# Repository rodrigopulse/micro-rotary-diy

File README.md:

# Micro Rotary

## How to Use:

1. Clone or download this repository.
2. Customize the `platformio.ini` file with your board settings.
3. Use PlatformIO CLI to compile, upload, and debug the firmware.

## Useful Commands

### Creating configuration files for VS Code:

```shell
platformio init --ide vscode
```

### Installing dependency libraries

```shell
pio run
```

### Uploading to Arduino

```shell
pio run --target upload
```

### Monitor

```shell
pio device monitor
```

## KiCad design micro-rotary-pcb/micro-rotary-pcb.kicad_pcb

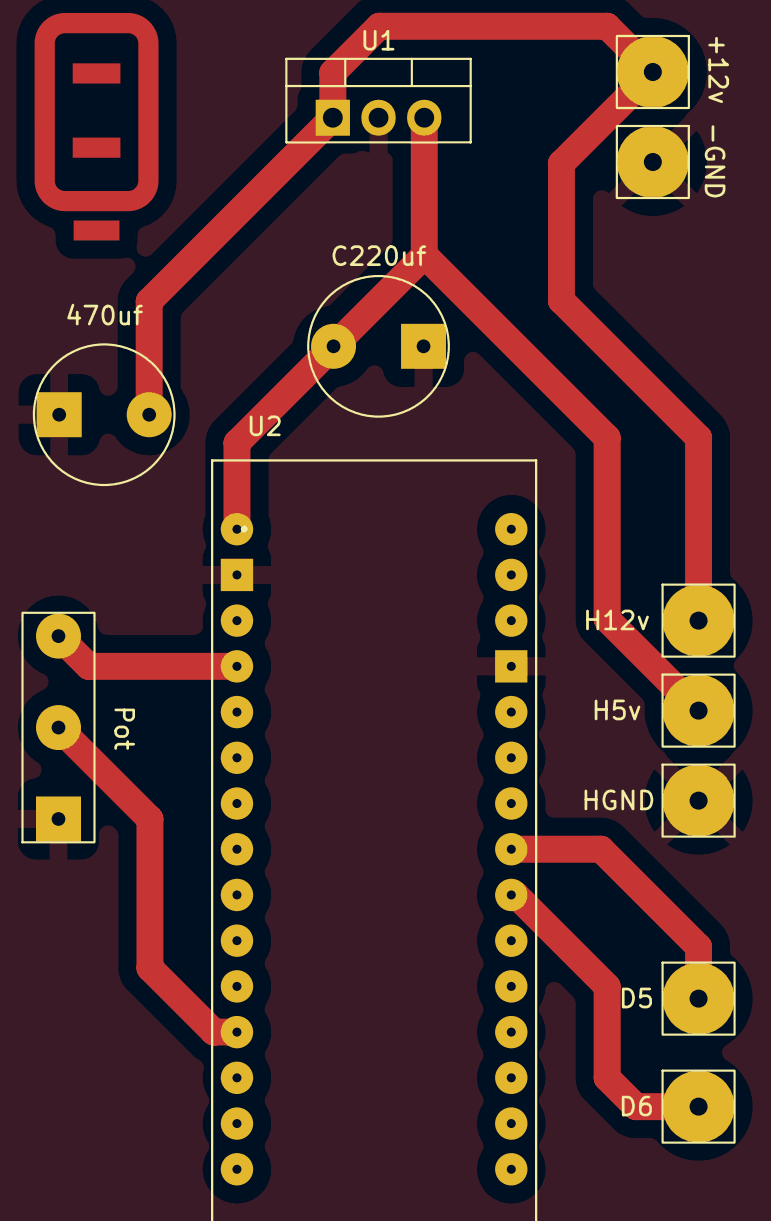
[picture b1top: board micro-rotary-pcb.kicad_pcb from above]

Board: 2 copper layers, 12 parts (0 on the bottom side), 8 nets.

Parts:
470uf: 470uf; Capacitor Polarized
+12v: Power 12v; Borne
-GND: Power GND; Borne
C220uf: 220uf; Capacitor Polarized
D5: D5; Borne
D6: D6; Borne
H5v: H 5v; Borne
H12v: H 12v; Borne
HGND: H GND; Borne
Pot: speed; Potentiometer
U1: L7805; TO-220-3_Vertical
U2: ARDUINO_NANO

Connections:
GND: 470uf.2, -GND.1, C220uf.2, HGND.1, Pot.3, U1.2 (GND), U2.4 (GND_4), U2.29 (GND_29)
unnamed: 470uf.1, +12v.1, H12v.1, U1.1 (IN)
unnamed: C220uf.1, H5v.1, U1.3 (OUT), U2.30 (VIN)
unnamed: Pot.1, U2.27 (+5V)
unnamed: Pot.2, U2.19 (A0)
unnamed: D5.1, U2.8 (D5)
unnamed: D6.1, U2.9 (D6)
unnamed: U2.3 (RESET), U2.28 (RESET)

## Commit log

2025-03-12 controlling motor speed
2025-03-12 change readme
2025-03-12 replaced NodeMCU with Arduino Nano
2025-03-12 pcb components
2025-03-12 remove kicad files
2025-03-12 gitignore modified
2025-03-18 remove serial and motor class
2025-03-18 fix vin
2025-03-19 fix gnd in pcb
2025-03-19 change arduino e potentiometer footprint
2025-03-21 fix inverted problem in pcb
